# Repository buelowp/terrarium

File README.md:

# Terrarium Control

The idea here is to provide a mechanism for controlling a small terrarium for plants that like humidity and warm. I'm doing this to control lights for a small planting of venus flytraps in my office. It provides a small bit of fun engineering for a simple mechanism.

## What's needed

1. WeMos D1 Mini (microcontroller)
1. 1.3 in OLED (Adafruit product id 938)
1. DHT22 (Temp and Humidity)
1. Soil Moisture Sensor (Sparkfun SEN-13322)
1. NeoPixel strip (Adafruit product id 1426)
1. UV LED 400nm (Sparkfun COM-08662)
1. 3v3 voltage regulator (Sparkfun COM-00526)
1. Power Supply (Sparkfun TOL-12889)
1. 1 x 470ohm 1/4 watt resistor
1. 2 x 1kohm 1/4 watt resistor
1. 1 x 10kohm 1/4 watt resistor
1. 2 x 2N3904 NPN Transistor (Sparkfun)
1. 1 x 100uf capacitor

## How to build it

The design is based on building a plastic terrarium from PVC and 3d printed parts. The 3d parts are a base and cap. There are 2 caps included, one that fits the OSH Park PCB, and one that would work with a standard breadboard solution. The 3d printed files include the .skp files if you want to make changes. The base contains the peat/soil, and the cap contains the electronics. The visible portion is 4 cut Plexi sheets (1/8 in) to fit the base and cap. These are fashioned into a box onto which the base and cap fit.

More to come.

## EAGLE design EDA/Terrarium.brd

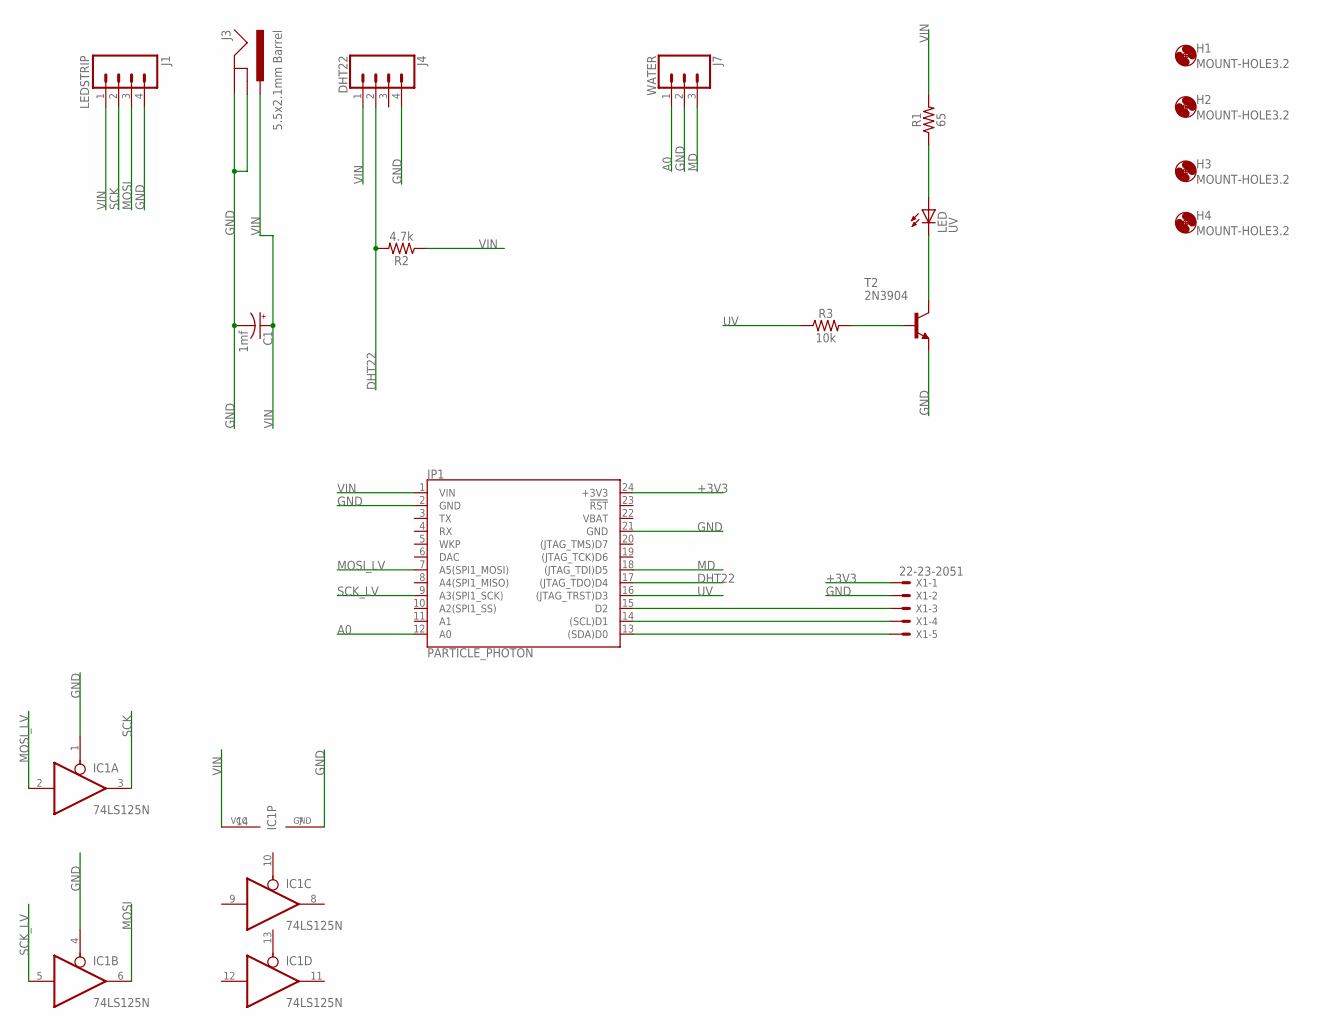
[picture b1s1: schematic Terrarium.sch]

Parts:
C1: 1mf; CPOL-RADIAL-5MM-10MM-KIT
H1, H2, H3, H4: MOUNT-HOLE3.2; 3,2
IC1: 74LS125N; DIL14
J1: LEDSTRIP; 1X04@1
J3: 5.5x2.1mm Barrel; POWER_JACK_SMD
J4: DHT22; 1X04
J7: WATER; 1X03
JP1: PARTICLE_PHOTON
LED: UV; LED5MM
R1: 65; AXIAL-0.3
R2: 4.7k; AXIAL-0.3
R3: 10k; AXIAL-0.3
T2: 2N3904; TO92
X1: 22-23-2051

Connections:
+3V3: JP1.24 (+3V3), X1.1
A0: J7.1, JP1.12 (A0)
DHT22: J4.2, JP1.17 ((JTAG_TDO)D4), R2.P$2 (2)
GND: C1.-, IC1.1 (OE), IC1.4 (OE), IC1.7 (GND), J1.4, J3.GND (GNDBREAK), J3.P$4 (GND), J4.4, J7.2, JP1.2 (GND), JP1.21 (GND), T2.3 (E), X1.2
MD: J7.3, JP1.18 ((JTAG_TDI)D5)
MOSI: IC1.6 (O), J1.3
MOSI_LV: IC1.2 (I), JP1.7 (A5(SPI1_MOSI))
unnamed: R3.P$2 (2), T2.2 (B)
unnamed: JP1.13 ((SDA)D0), X1.5
unnamed: LED.K (C), T2.1 (C)
unnamed: LED.A, R1.P$1 (1)
unnamed: JP1.14 ((SCL)D1), X1.4
unnamed: JP1.15 (D2), X1.3
SCK: IC1.3 (O), J1.2
SCK_LV: IC1.5 (I), JP1.9 (A3(SPI1_SCK))
UV: JP1.16 ((JTAG_TRST)D3), R3.P$1 (1)
VBAT: JP1.22 (VBAT)
VIN: C1.+, IC1.14 (VCC), J1.1, J3.VIN0 (PWR), J4.1, JP1.1 (VIN), R1.P$2 (2), R2.P$1 (1)

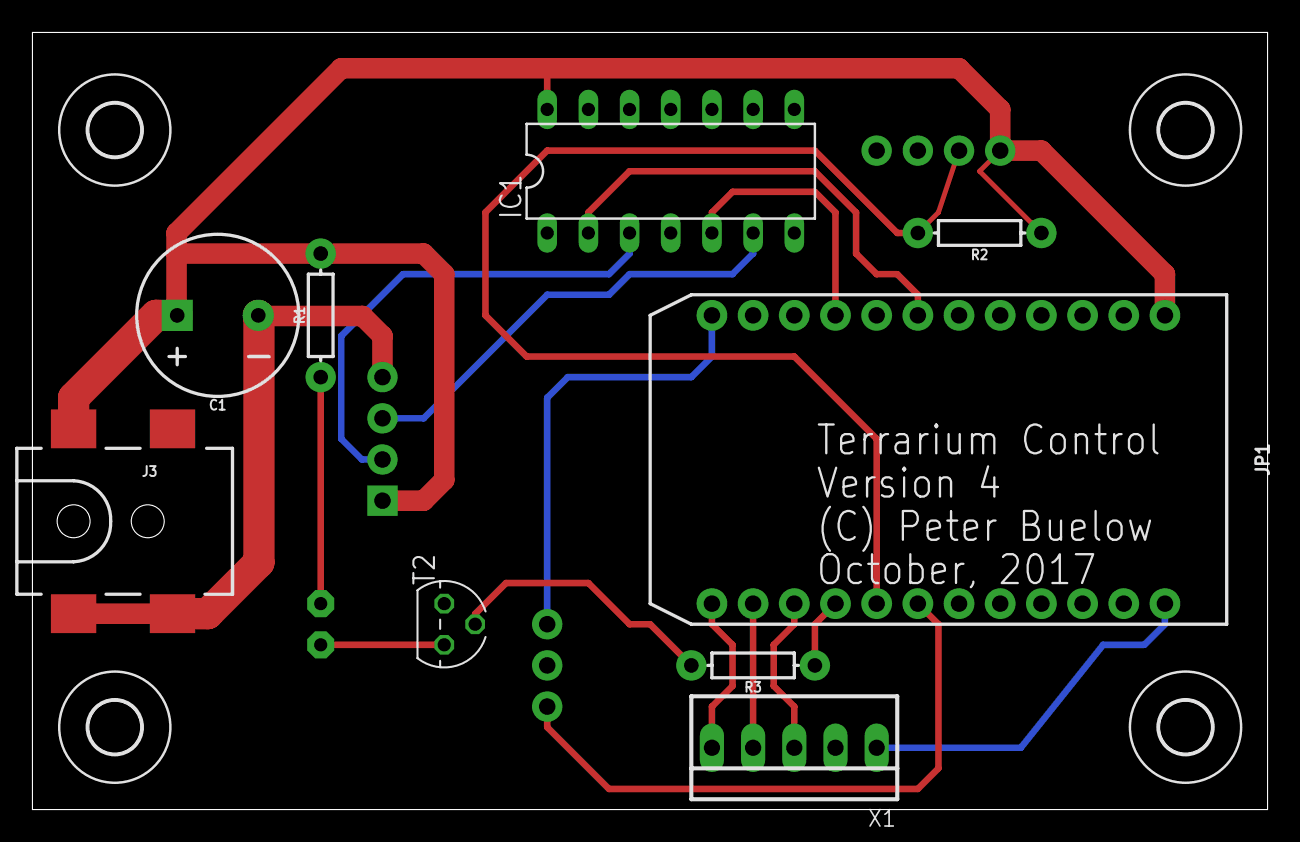
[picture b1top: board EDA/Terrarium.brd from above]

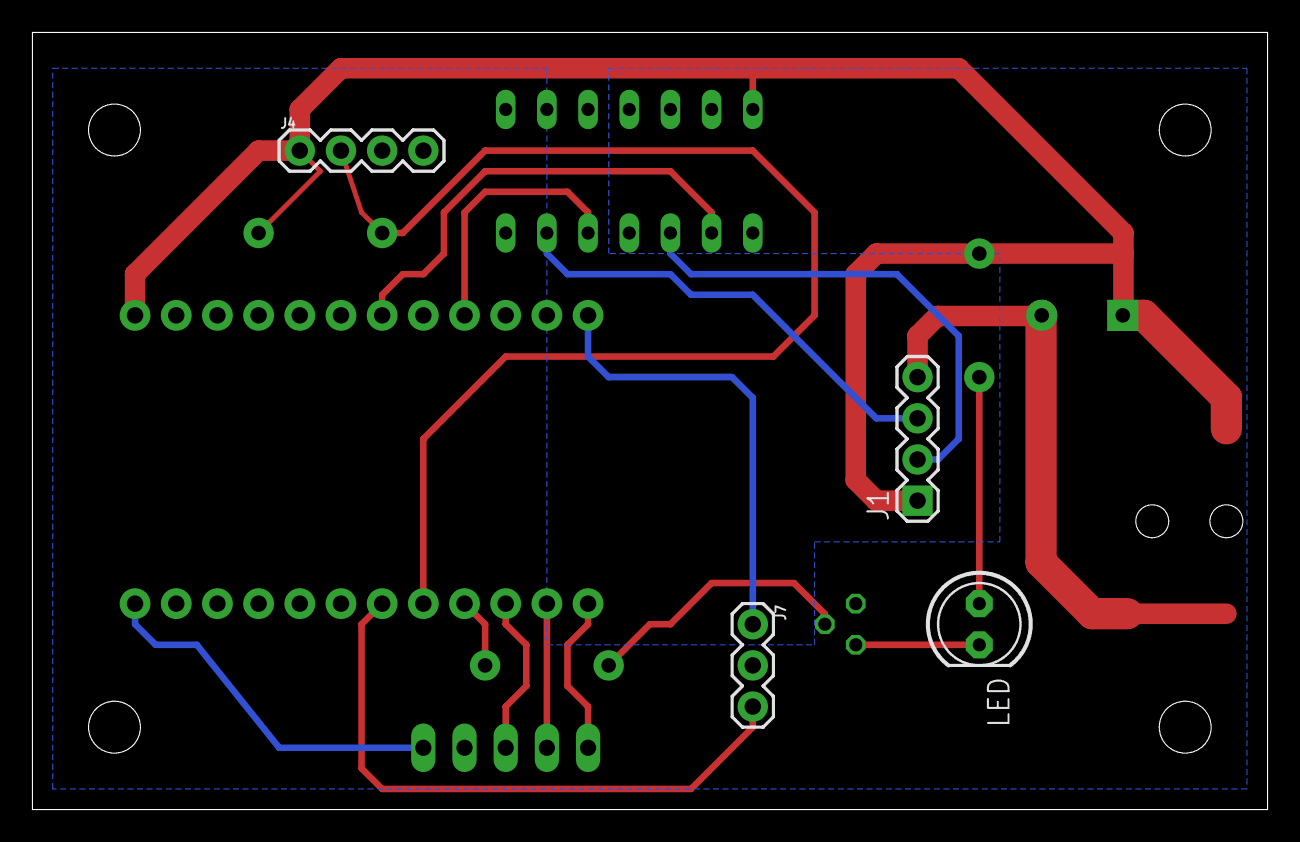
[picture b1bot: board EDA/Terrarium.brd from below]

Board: 2 copper layers, 76.2 x 47.9 mm, 17 parts (4 on the bottom side), 17 nets.

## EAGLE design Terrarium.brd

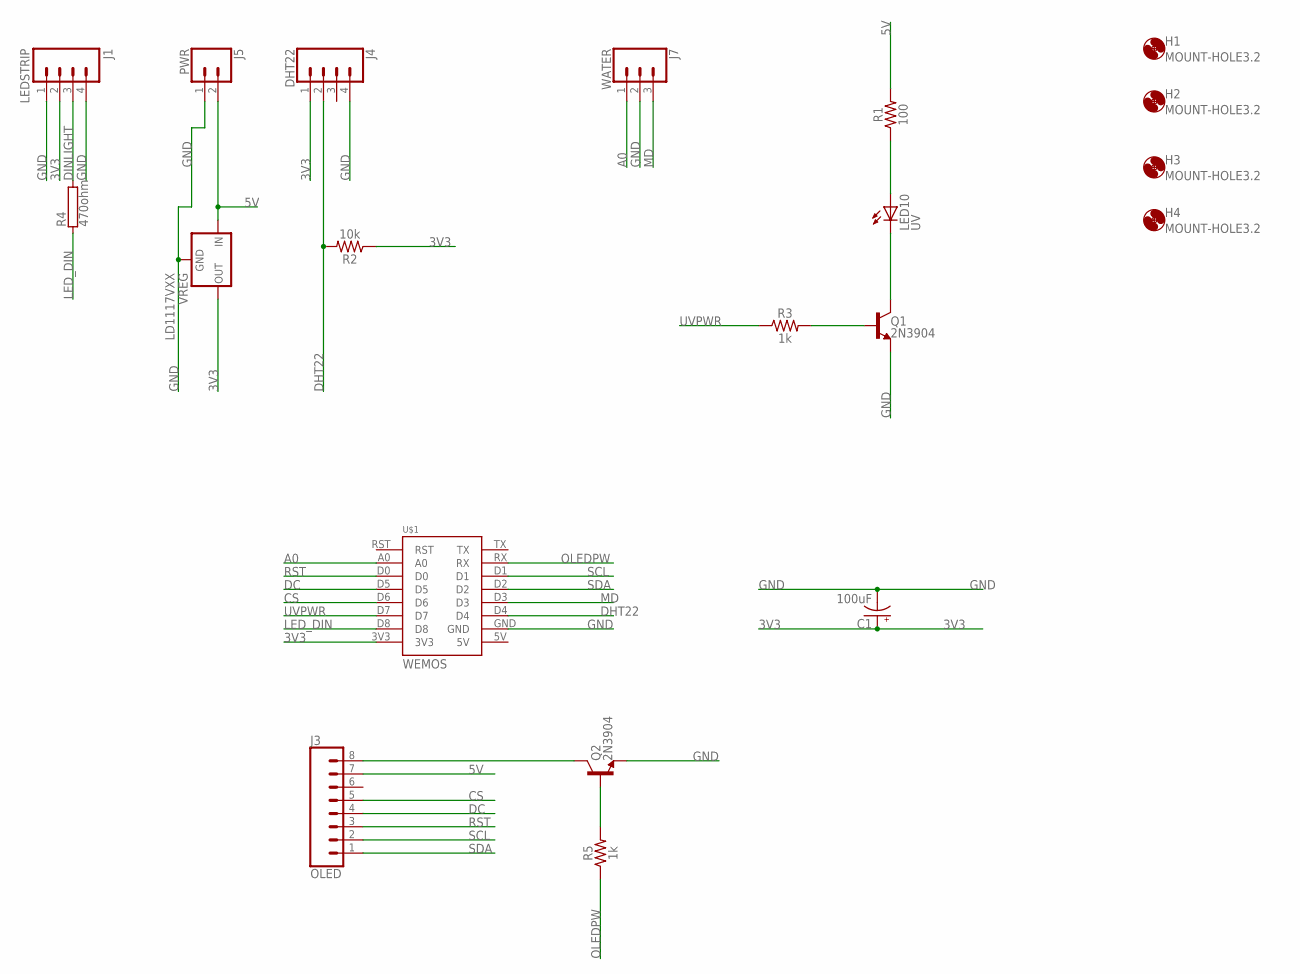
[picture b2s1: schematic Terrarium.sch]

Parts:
C1: 100uF; CPOL-RADIAL-2.5MM-6.5MM
H1, H2, H3, H4: MOUNT-HOLE3.2; 3,2
J1: LEDSTRIP; 1X04@1
J3: OLED; 1X08
J4: DHT22; 1X04
J5: PWR; 1X02
J7: WATER; 1X03
LED10: UV; LED5MM
Q1, Q2: 2N3904; TO-92
R1: 100; AXIAL-0.3
R2: 10k; AXIAL-0.3
R3, R5: 1k; AXIAL-0.3
R4: 470ohm; RS1/4
U$1: WEMOS
VREG: LD1117VXX; 78XXL

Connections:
3V3: C1.1 (+), J1.2, J4.1, R2.P$1 (1), U$1.3V3, VREG.GND (OUT)
5V: J3.7, J5.2, R1.P$2 (2), VREG.OUT (IN)
A0: J7.1, U$1.A0
CS: J3.5, U$1.D6
DC: J3.4, U$1.D5
DHT22: J4.2, R2.P$2 (2), U$1.D4
DINLIGHT: J1.3, R4.2
GND: C1.2 (-), J1.1, J1.4, J4.4, J5.1, J7.2, Q1.1 (E), Q2.1 (E), U$1.GND, VREG.IN (GND)
LED_DIN: R4.1, U$1.D8
MD: J7.3, U$1.D3
unnamed: J3.8, Q2.3 (C)
unnamed: Q1.2 (B), R3.P$2 (2)
unnamed: LED10.K (C), Q1.3 (C)
unnamed: LED10.A, R1.P$1 (1)
unnamed: Q2.2 (B), R5.P$2 (2)
OLEDPW: R5.P$1 (1), U$1.RX
RST: J3.3, U$1.D0
SCL: J3.2, U$1.D1
SDA: J3.1, U$1.D2
UVPWR: R3.P$1 (1), U$1.D7

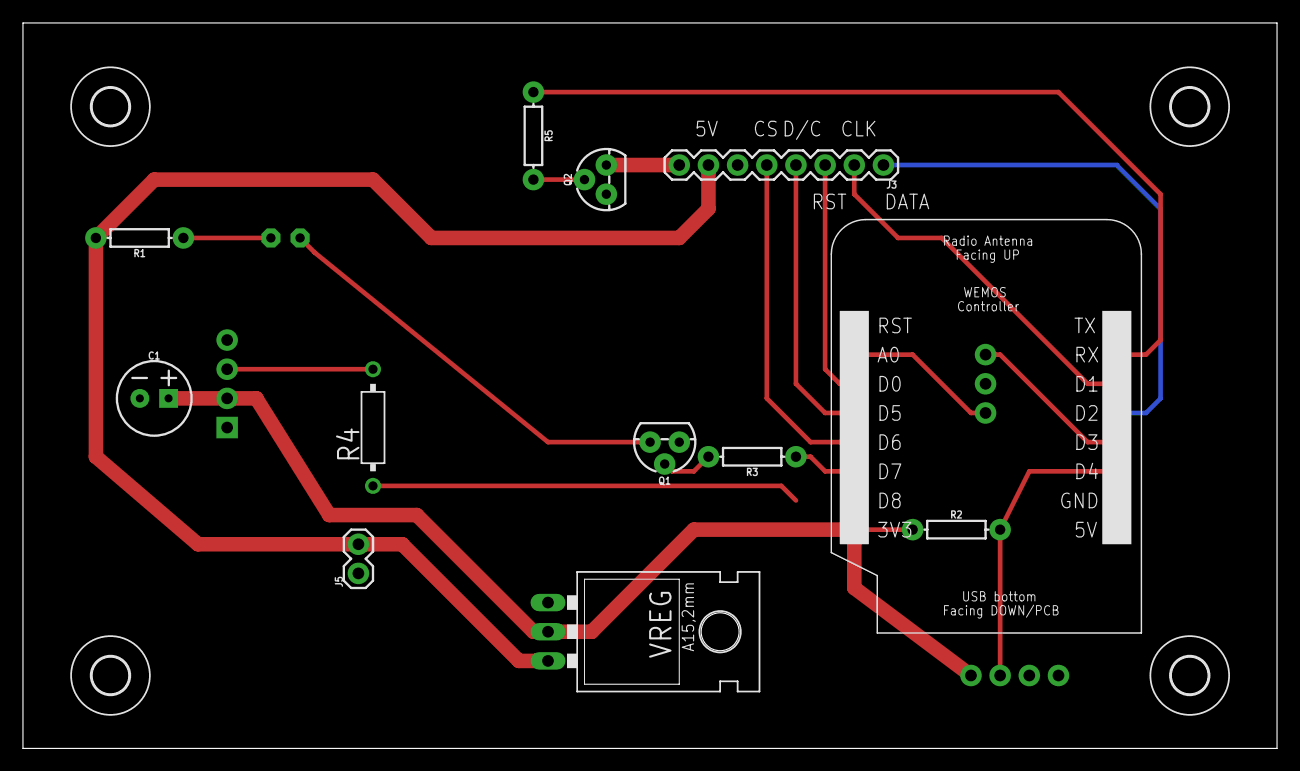
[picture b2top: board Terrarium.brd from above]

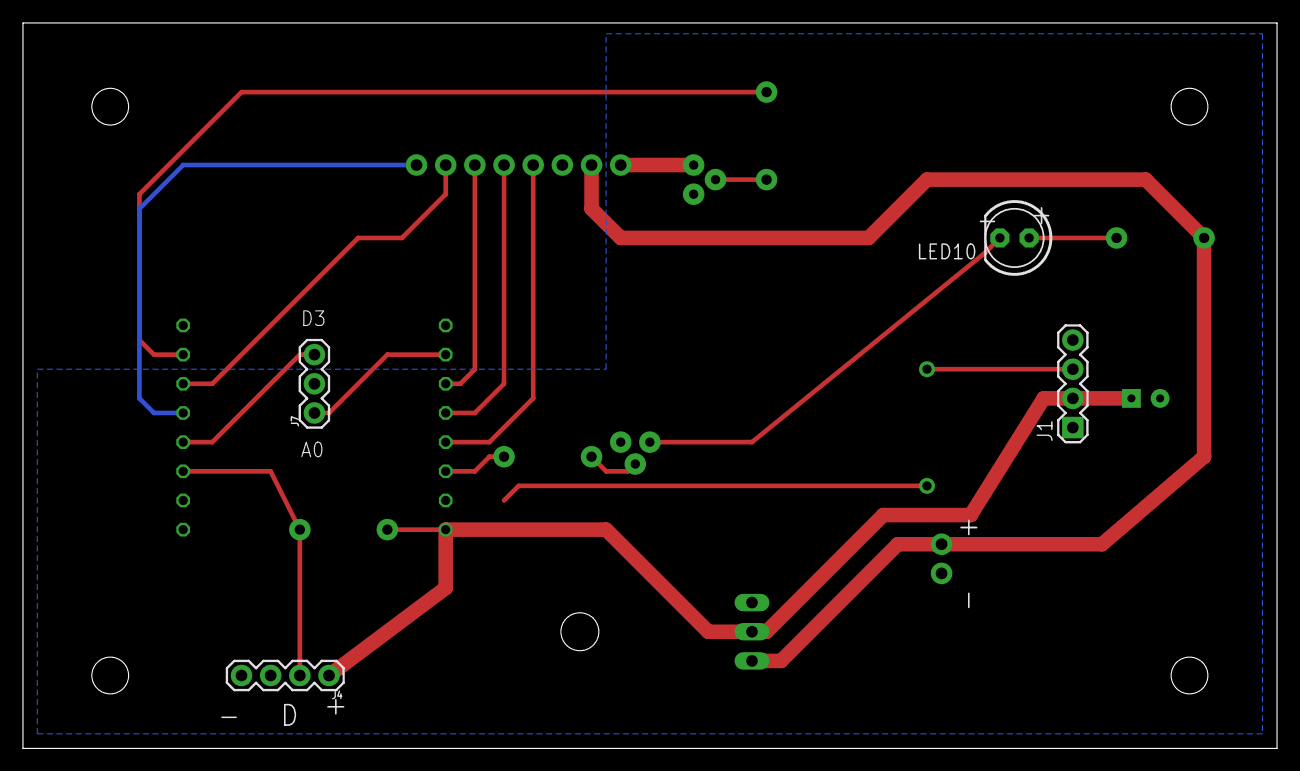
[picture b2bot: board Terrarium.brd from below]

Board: 2 copper layers, 109.2 x 63.2 mm, 20 parts (4 on the bottom side), 20 nets.

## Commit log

2017-01-12 Adding code
2017-01-12 Lots of changes
    Added the Eagle files
    Updated to use PIN names instead of the Wemos pin designations
    Updated logic for turning the lights on and off at sunrise/sunset
    Added sunrise and sunset calculation
    Code cleanup and bugfixes
2017-01-12 Updated the README
2017-01-12 Adding the sketchup files for the base and cap
2017-01-12 License update
2017-01-12 Adding STL files for the cap and base. Updated the cap and base to latest
2017-01-15 Some build fixes. Pins will change though as I update the pcb though.
2017-01-26 Fixed a sunrise/sunset bug
2017-01-27 Checkpoint. Still doesn't work exactly right.
2017-01-27 Fixed the sunrise/sunset bug
2017-10-28 Lots of Photon fix ups
    1. Added correct i2c handling for OLED
    2. Changed pins to match new layout
    3. Starting changes for light bar
2017-10-28 Continuing improvements
    1. Update Eagle files for new layout
    2. Update text placement on OLED
2017-10-29 Fixes and some debug variables
2017-10-29 Ask the Photon to sync time every hour to avoid drift.
2017-10-29 Fixed a calculation bug with sunrise
2017-10-31 Clear the display before we go to sleep.
2018-07-07 Pushing latest

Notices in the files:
parts and their libraries:
SparkFun-Connectors: Licensing: Creative Commons ShareAlike 4.0 International - https://creativecommons.org/licenses/by-sa/4.0
